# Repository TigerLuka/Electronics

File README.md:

When making a new PCB board, please import corresponding PCB board constraints
from "Board Templates/JLC" if the board is to be manufactured by JLC.

Download git

Create a token in github so you can pull the repository in git bash

------------------------

INSIDE GIT BASH TERMINAL

git clone https://github.com/LSUTigerRacing/Electronics.git

cd Electronics

Highlight and right click on FSAE_ELECTRONICS in git bash terminal to open file location and find KiCAD project

------------------------

MAKE ALL EDITS TO LOCAL COPY HERE

------------------------

OPEN GIT BASH TERMINAL WHEN FINISHED

cd Electronics

git checkout -b "Branch Name"

git add .

git commit -m "Description of work done in commit"

git push -u origin "Branch Name"

DELETE LOCAL COPY

------------------------

REPEAT

------------------------

TO MERGE:

go to branches tab

go to branches that you push

make a pull request

go into pull request

marge if no issues

delete branch 

# FAULT LATCH

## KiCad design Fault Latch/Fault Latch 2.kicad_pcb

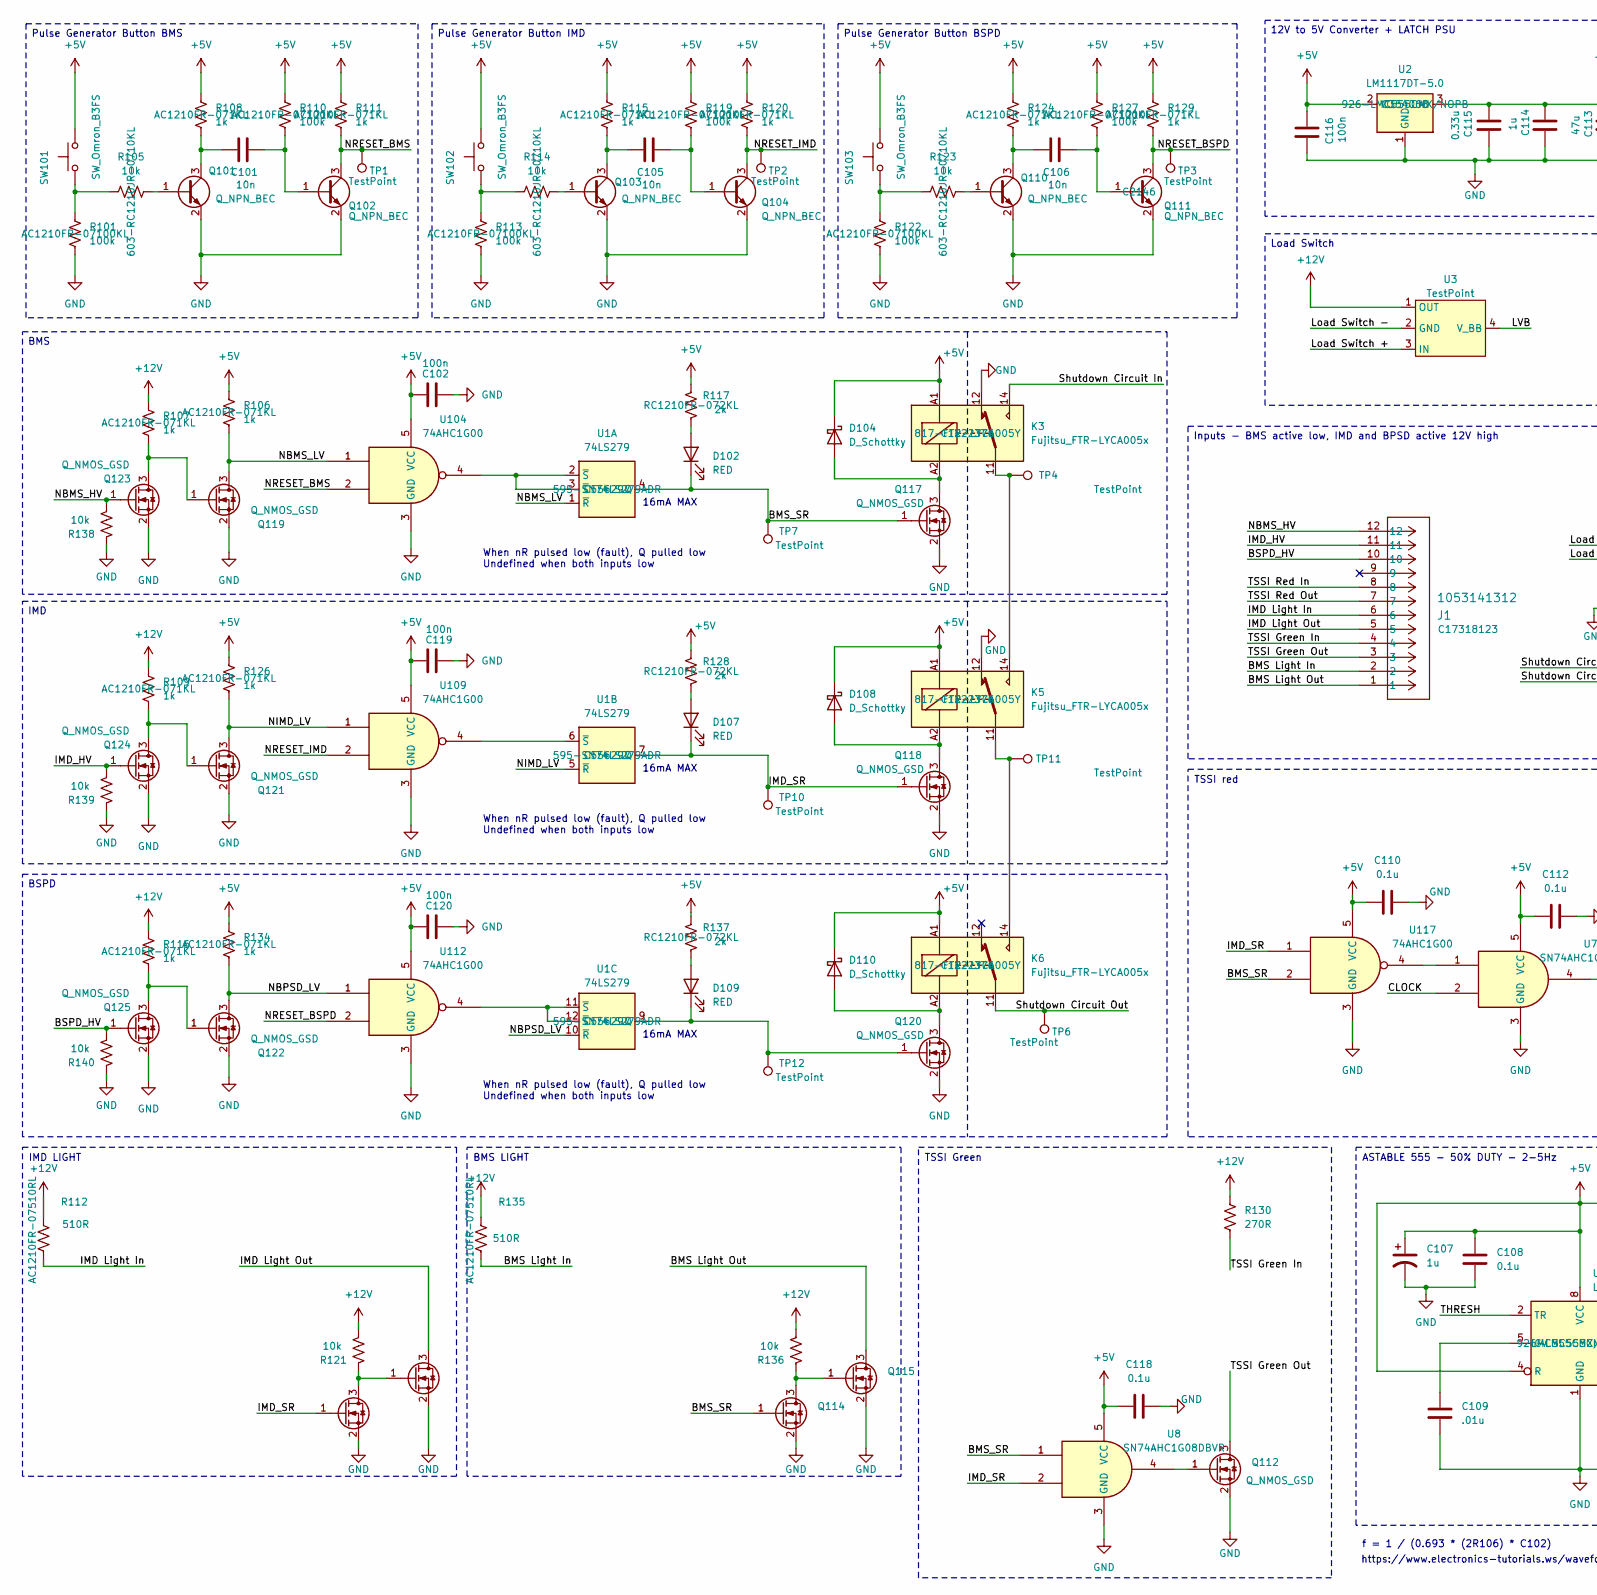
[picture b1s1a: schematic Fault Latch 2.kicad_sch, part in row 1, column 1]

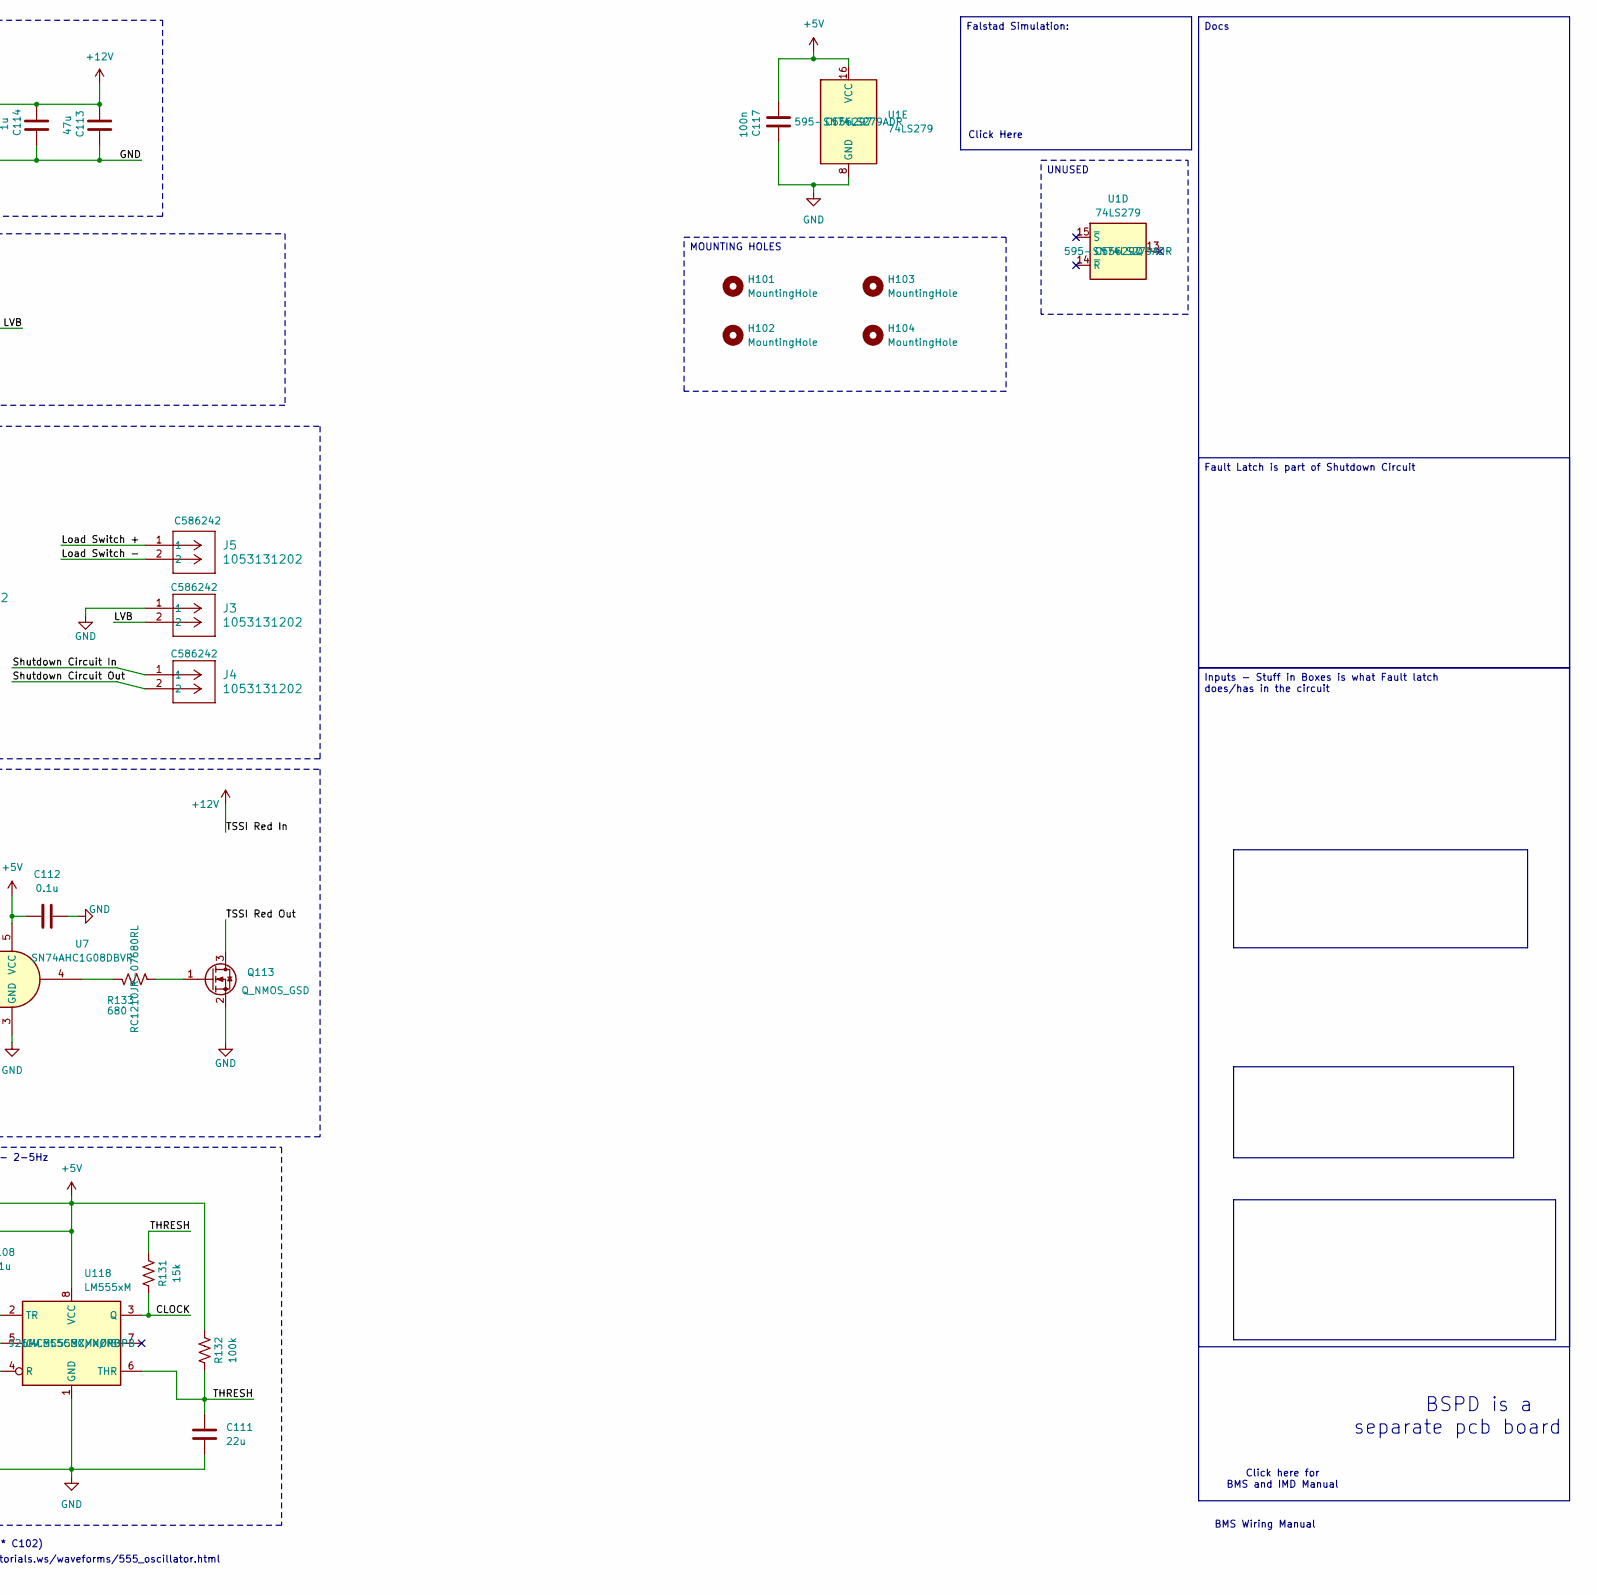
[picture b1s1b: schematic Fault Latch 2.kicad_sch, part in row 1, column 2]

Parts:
C101, C105, C106: 10n; C_0603_1608Metric_Pad1.08x0.95mm_HandSolder; JLC# C1589
C102, C116, C117, C119, C120: 100n; C_0603_1608Metric_Pad1.08x0.95mm_HandSolder; JLC# C1591
C107: 1u; C_0402_1005Metric; JLC# C59782
C108, C110, C112, C118: 0.1u; C_0402_1005Metric; JLC# C133086
C109: .01u; C_0402_1005Metric; JLC# C15195
C111: 22u; C_0402_1005Metric; JLC# C105226
C113: 47u; CP_Elec_6.3x5.4; JLC# C2836440
C114: 1u; C_0805_2012Metric_Pad1.18x1.45mm_HandSolder; JLC# C91186
C115: 0.33u; C_0603_1608Metric_Pad1.08x0.95mm_HandSolder; JLC# C282682
D102, D107, D109: RED; LED_0805_2012Metric_Pad1.15x1.40mm_HandSolder; JLC# C19171391
D104, D108, D110: D_Schottky; D_SMA; JLC# C8678
H101, H102, H103, H104: MountingHole; MountingHole_3.2mm_M3
J1: 1053141312; CONN_SD-105314-100_12_MOL; MOUSER 538-105314-1312
J3, J4, J5: 1053131202; Molex_Nano-Fit_105313-xx02_1x02_P2.50mm_Horizontal; MOUSER 538-105313-1202
K3, K5, K6: Fujitsu_FTR-LYCA005x; Relay_SPDT_Fujitsu_FTR-LYCA005x_FormC_Vertical; MOUSER 817-FTR-LYCA005Y
Q101, Q102, Q103, Q104, Q110, Q111: Q_NPN_BEC; SOT-23; JLC# C2146
Q105, Q106, Q112, Q113, Q114, Q115, Q117, Q118, Q119, Q120, Q121, Q122, Q123, Q124, Q125: Q_NMOS_GSD; SOT-23; JLC# C151421
R101, R110, R113, R119, R122, R127, R132: 100k; R_1210_3225Metric; JLC# C230004
R105, R114, R121, R123, R136, R138, R139, R140: 10k; R_1210_3225Metric; JLC# C137088
R106, R107, R108, R109, R111, R115, R116, R120, R124, R126, R129, R134: 1k; R_1210_3225Metric; JLC# C230096
R112, R135: 510R; R_1210_3225Metric; JLC# C230277
R117, R128, R137: 2k; R_1210_3225Metric; JLC# C137097
R130: 270R; R_1210_3225Metric; JLC# C230144
R131: 15k; R_1210_3225Metric; JLC# C230040
R133: 680; R_1210_3225Metric; JLC# C137071
SW101, SW102, SW103: SW_Omron_B3FS; SW_SPST_Omron_B3FS-100xP; JLC# C271750
TP1, TP2, TP3, TP4, TP6, TP7, TP10, TP11, TP12: TestPoint; TestPoint_Pad_D1.5mm
U1: 74LS279; SOIC-16_3.9x9.9mm_P1.27mm; MOUSER 595-SN74LS279ADR
U2: LM1117DT-5.0; TO-252-3_TabPin2; JLC# C354068
U3: TestPoint; TestPoint_Pad_D1.5mm
U7, U8: SN74AHC1G08DBVR; SOT-23-5; JLC# C7467
U104, U109, U112, U117: 74AHC1G00; SOT-23-5; JLC# C350556
U118: LM555xM; SOIC-8_3.9x4.9mm_P1.27mm; Mouser Part Number 926-LMC555CMX/NOPB; JLC# C90760

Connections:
+5V: C102.1, C107.1, C108.1, C110.2, C112.2, C116.2, C117.1, C118.2, C119.1, C120.1, D104.1 (K), D108.1 (K), D110.1 (K), K3.A1, K5.A1, K6.A1, R106.1, R108.1, R110.1, R111.1, R115.1, R117.2, R119.1, R120.1, R124.1, R126.1, R127.1, R128.2, R129.1, R132.2, R134.1, R137.2, SW101.2, SW102.2, SW103.2, U1.16 (VCC), U2.2 (VO), U7.5 (VCC), U8.5 (VCC), U104.5 (VCC), U109.5 (VCC), U112.5 (VCC), U117.5 (VCC), U118.4 (R), U118.8 (VCC)
+12V: C113.1, C114.1, C115.1, J1.8, R107.1, R109.1, R112.1, R116.1, R121.1, R130.2, R135.1, R136.1, U2.3 (VI), U3.1 (OUT)
/BMS Light In: J1.2, R135.2
/BMS Light Out: J1.1, Q115.3 (D)
/BMS_SR: D102.1 (K), Q114.1 (G), Q117.1 (G), TP7.1, U1.4 (Q), U8.1, U117.2
/BSPD_HV: J1.10, Q125.1 (G), R140.1
/CLOCK: R131.1, U7.2, U118.3 (Q)
/IMD Light In: J1.6, R112.2
/IMD Light Out: J1.5, Q106.3 (D)
/IMD_HV: J1.11, Q124.1 (G), R139.1
/IMD_SR: D107.1 (K), Q105.1 (G), Q118.1 (G), TP10.1, U1.7 (Q), U8.2, U117.1
/LVB: J3.2, U3.4 (V_BB)
/Load Switch +: J5.1, U3.3 (IN)
/Load Switch -: J5.2, U3.2 (GND)
/NBMS_HV: J1.12, Q123.1 (G), R138.1
/NBMS_LV: Q119.3 (D), R106.2, U1.1 (~R), U104.1
/NBPSD_LV: Q122.3 (D), R134.2, U1.10 (~R), U112.1
/NIMD_LV: Q121.3 (D), R126.2, U1.5 (~R), U109.1
/NRESET_BMS: Q102.3 (C), R111.2, TP1.1, U104.2
/NRESET_BSPD: Q111.3 (C), R129.2, TP3.1, U112.2
/NRESET_IMD: Q104.3 (C), R120.2, TP2.1, U109.2
/Shutdown Circuit In: J4.1, K3.14
/Shutdown Circuit Out: J4.2, K6.11, TP6.1
/THRESH: C111.2, R131.2, R132.1, U118.2 (TR), U118.6 (THR)
/TSSI Green In: J1.4, R130.1
/TSSI Green Out: J1.3, Q112.3 (D)
/TSSI Red Out: J1.7, Q113.3 (D)
GND: C102.2, C107.2, C108.2, C109.2, C110.1, C111.1, C112.1, C113.2, C114.2, C115.2, C116.1, C117.2, C118.1, C119.2, C120.2, J3.1, K3.12, K5.12, Q101.2 (E), Q102.2 (E), Q103.2 (E), Q104.2 (E), Q105.2 (S), Q106.2 (S), Q110.2 (E), Q111.2 (E), Q112.2 (S), Q113.2 (S), Q114.2 (S), Q115.2 (S), Q117.2 (S), Q118.2 (S), Q119.2 (S), Q120.2 (S), Q121.2 (S), Q122.2 (S), Q123.2 (S), Q124.2 (S), Q125.2 (S), R101.2, R113.2, R122.2, R138.2, R139.2, R140.2, U1.8 (GND), U2.1 (GND), U7.3 (GND), U8.3 (GND), U104.3 (GND), U109.3 (GND), U112.3 (GND), U117.3 (GND), U118.1 (GND)
unnamed: D102.2 (A), R117.1
unnamed: D104.2 (A), K3.A2, Q117.3 (D)
unnamed: D107.2 (A), R128.1
unnamed: D108.2 (A), K5.A2, Q118.3 (D)
unnamed: D109.2 (A), R137.1
unnamed: D109.1 (K), Q120.1 (G), TP12.1, U1.9 (Q)
unnamed: D110.2 (A), K6.A2, Q120.3 (D)
unnamed: K3.11, K5.14, TP4.1
unnamed: K5.11, K6.14, TP11.1
unnamed: Q101.1 (B), R105.1
unnamed: C101.1, Q101.3 (C), R108.2
unnamed: C101.2, Q102.1 (B), R110.2
unnamed: Q103.1 (B), R114.1
unnamed: C105.1, Q103.3 (C), R115.2
unnamed: C105.2, Q104.1 (B), R119.2
unnamed: Q105.3 (D), Q106.1 (G), R121.2
unnamed: Q110.1 (B), R123.1
unnamed: C106.1, Q110.3 (C), R124.2
unnamed: C106.2, Q111.1 (B), R127.2
unnamed: Q112.1 (G), U8.4
unnamed: Q113.1 (G), R133.1
unnamed: Q114.3 (D), Q115.1 (G), R136.2
unnamed: Q119.1 (G), Q123.3 (D), R107.2
unnamed: Q121.1 (G), Q124.3 (D), R109.2
unnamed: Q122.1 (G), Q125.3 (D), R116.2
unnamed: R101.1, R105.2, SW101.1
unnamed: R113.1, R114.2, SW102.1
unnamed: R122.1, R123.2, SW103.1
unnamed: R133.2, U7.4
unnamed: U1.6 (~S), U109.4
unnamed: U1.2 (~S), U1.3 (~S), U104.4
unnamed: U1.11 (~S), U1.12 (~S), U112.4
unnamed: U7.1, U117.4
unnamed: C109.1, U118.5 (CV)

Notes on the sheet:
16mA MAX
BMS Wiring Manual
When nR pulsed low (fault), Q pulled low Undefined when both inputs low
Click here for BMS and IMD Manual
BSPD is a separate pcb board
f = 1 / (0.693 * (2R106) * C102)
https://www.electronics-tutorials.ws/waveforms/555_oscillator.html
Click Here
UNUSED
Pulse Generator Button BMS
Inputs - Stuff in Boxes is what Fault latch does/has in the circuit
TSSI red
BSPD
BMS
Load Switch
Pulse Generator Button BSPD
TSSI Green
ASTABLE 555 - 50% DUTY - 2-5Hz
Fault Latch is part of Shutdown Circuit
Docs
Pulse Generator Button IMD
12V to 5V Converter + LATCH PSU
MOUNTING HOLES
Inputs - BMS active low, IMD and BPSD active 12V high
BMS LIGHT
IMD
Falstad Simulation:
IMD LIGHT

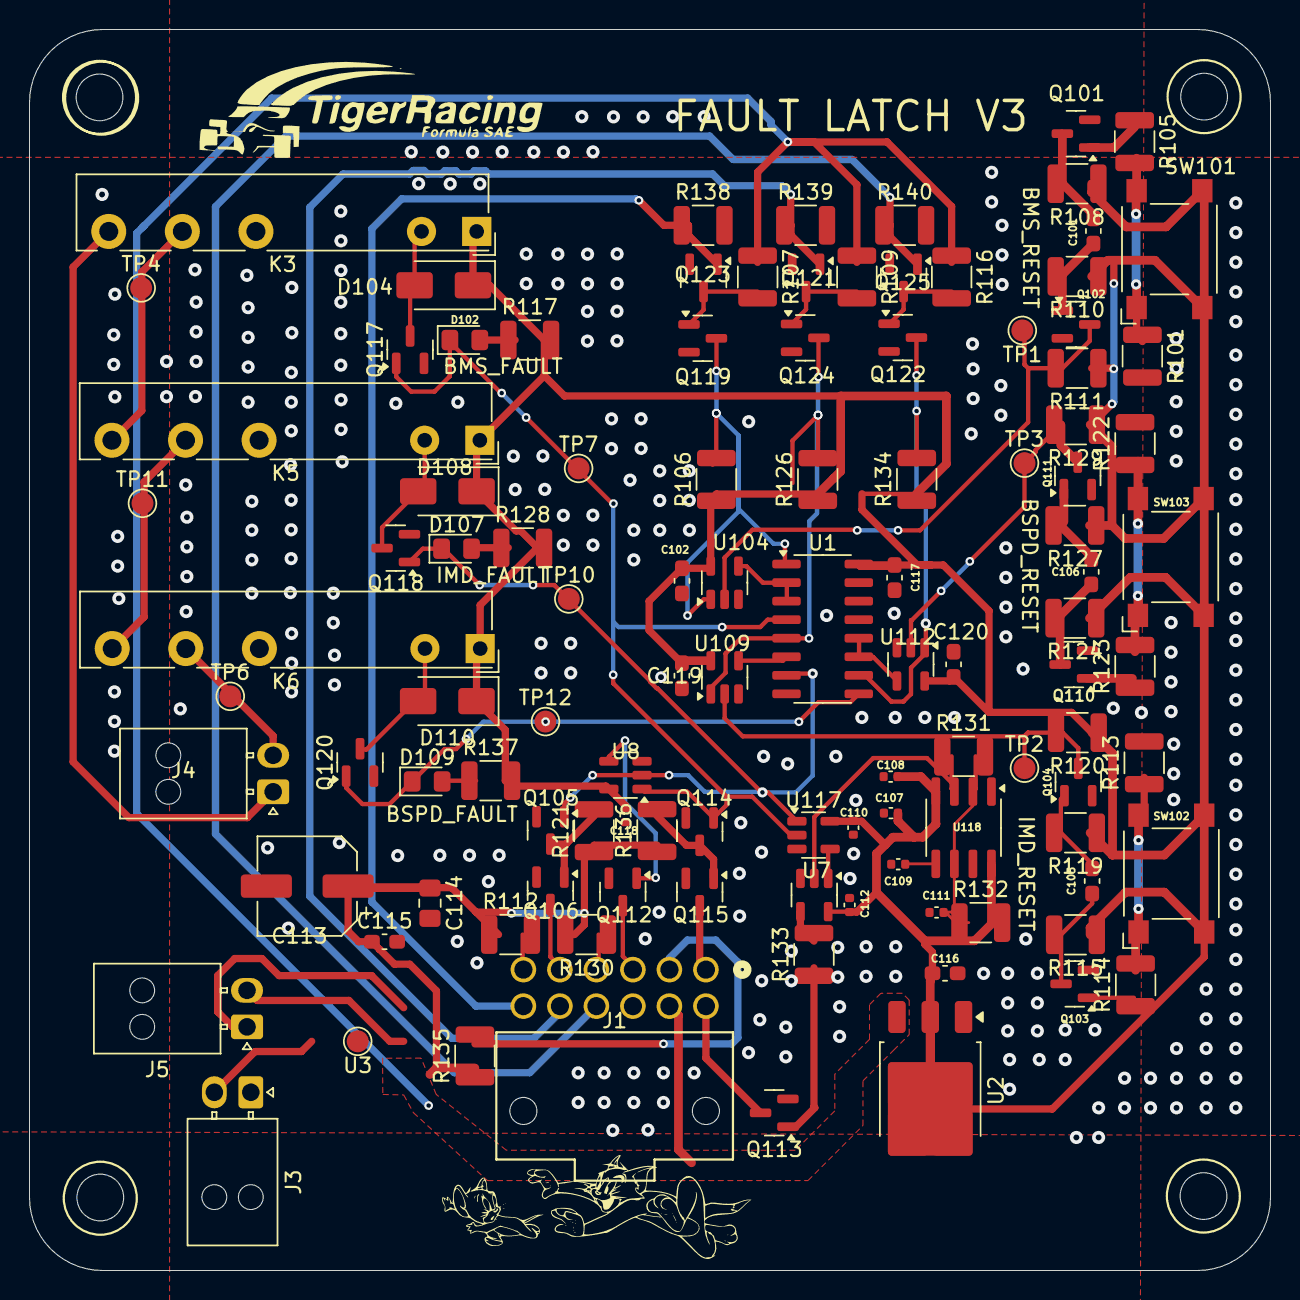
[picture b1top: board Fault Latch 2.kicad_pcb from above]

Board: 2 copper layers, 85.0 x 85.0 mm, 113 parts (0 on the bottom side), 59 nets.

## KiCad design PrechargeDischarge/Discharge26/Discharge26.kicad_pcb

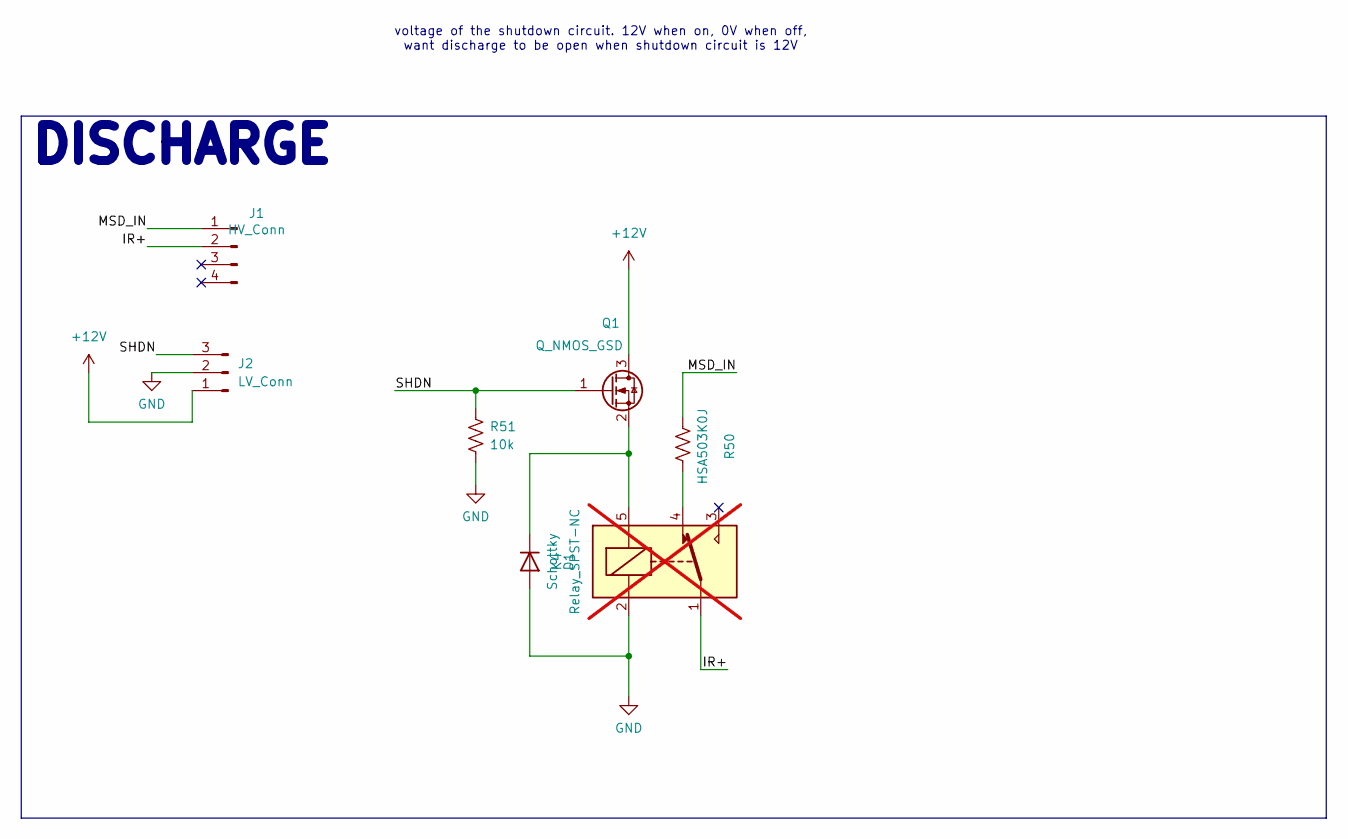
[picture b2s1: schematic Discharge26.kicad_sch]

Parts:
D1: Schottky; D_SMA; JLC C8678
J1: HV_Conn; MicroFit_4pin
J2: LV_Conn; Molex_Nano-Fit_105313-xx03_1x03_P2.50mm_Horizontal; JLC C561764
K4: Relay_SPST-NC; Discharge_relay; not fitted
Q1: Q_NMOS_GSD; SOT-23; JLC# C8545
R50: HSA503K0J; Discharge_Resistor
R51: 10k; R_1206_3216Metric

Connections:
+12V: J2.1, Q1.3 (D)
/IR+: J1.2, K4.1
/MSD_IN: J1.1, R50.2
/SHDN: J2.3, Q1.1 (G), R51.1
GND: D1.2 (A), J2.2, K4.2, R51.2
unnamed: D1.1 (K), K4.5, Q1.2 (S)
unnamed: K4.4, R50.1

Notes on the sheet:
voltage of the shutdown circuit. 12V when on, 0V when off, want discharge to be open when shutdown circuit is 12V
DISCHARGE

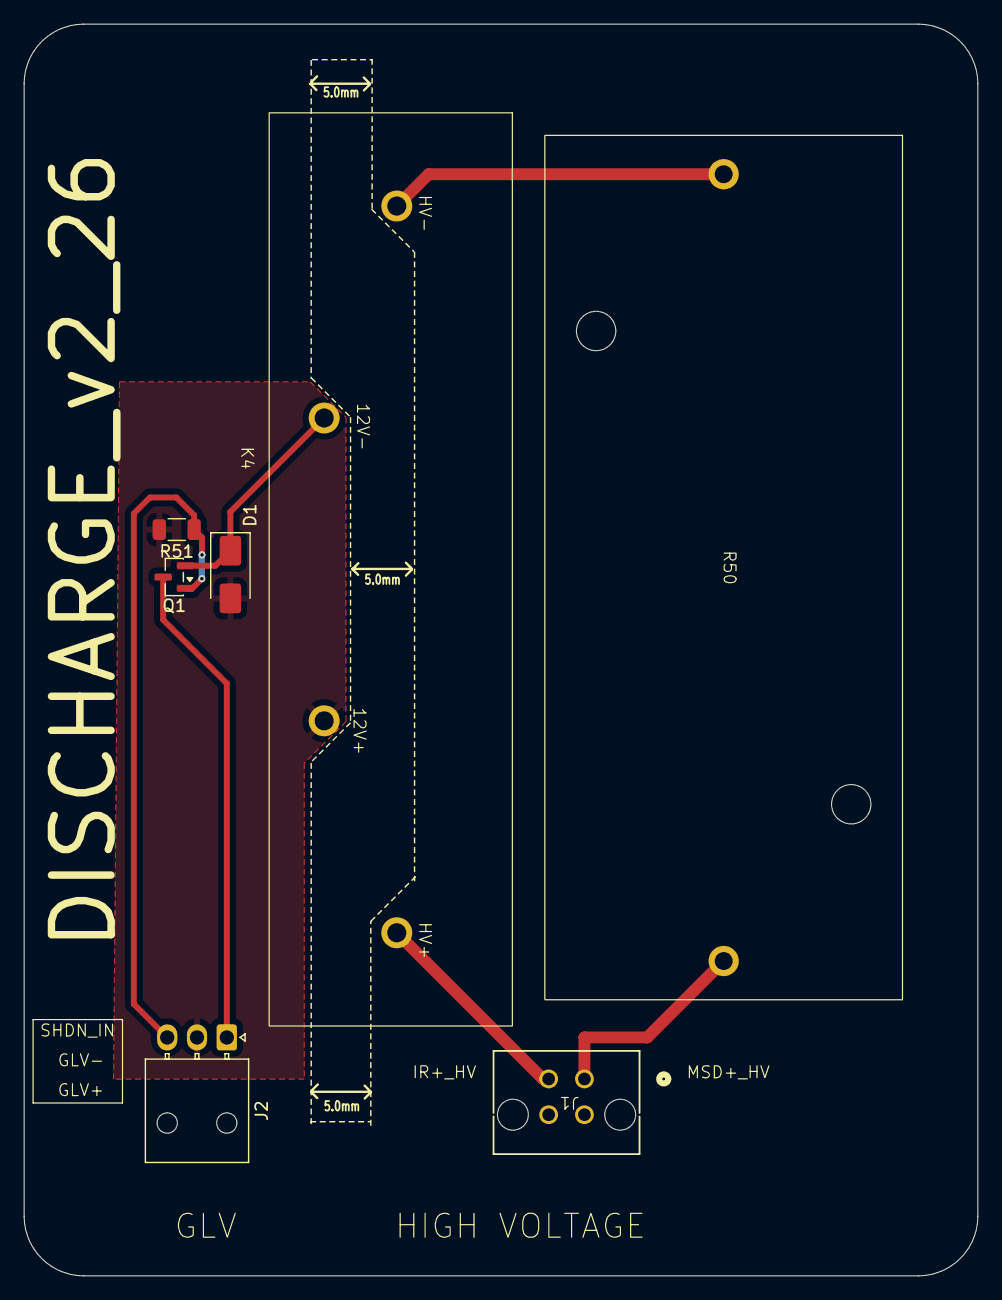
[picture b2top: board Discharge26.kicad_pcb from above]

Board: 2 copper layers, 80.0 x 105.0 mm, 7 parts (0 on the bottom side), 7 nets.

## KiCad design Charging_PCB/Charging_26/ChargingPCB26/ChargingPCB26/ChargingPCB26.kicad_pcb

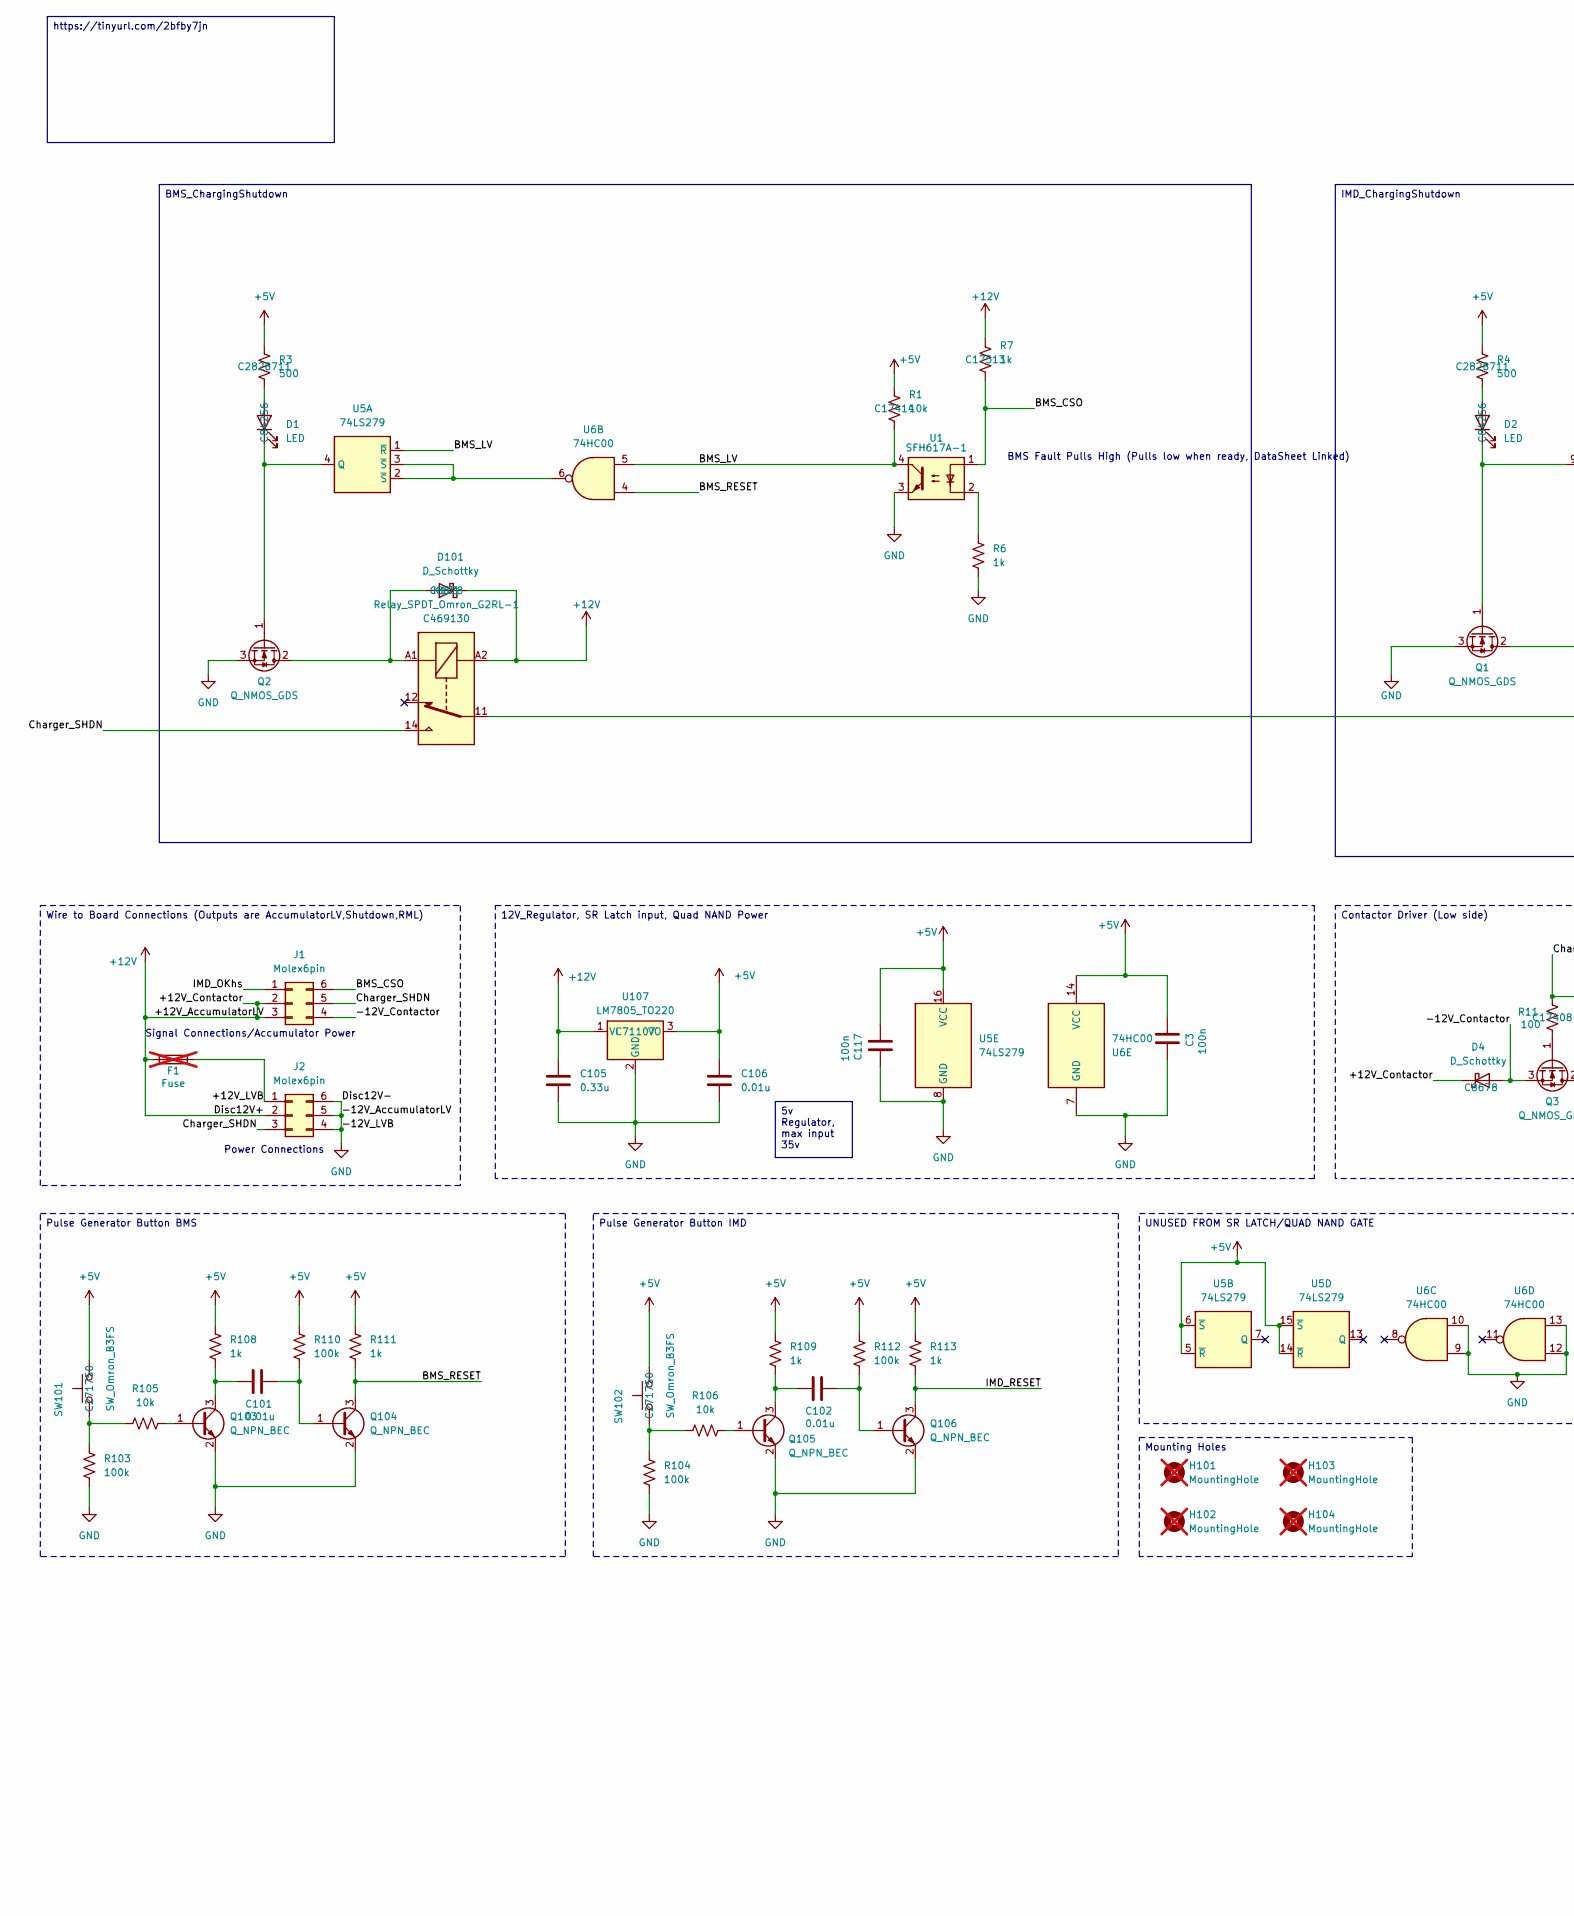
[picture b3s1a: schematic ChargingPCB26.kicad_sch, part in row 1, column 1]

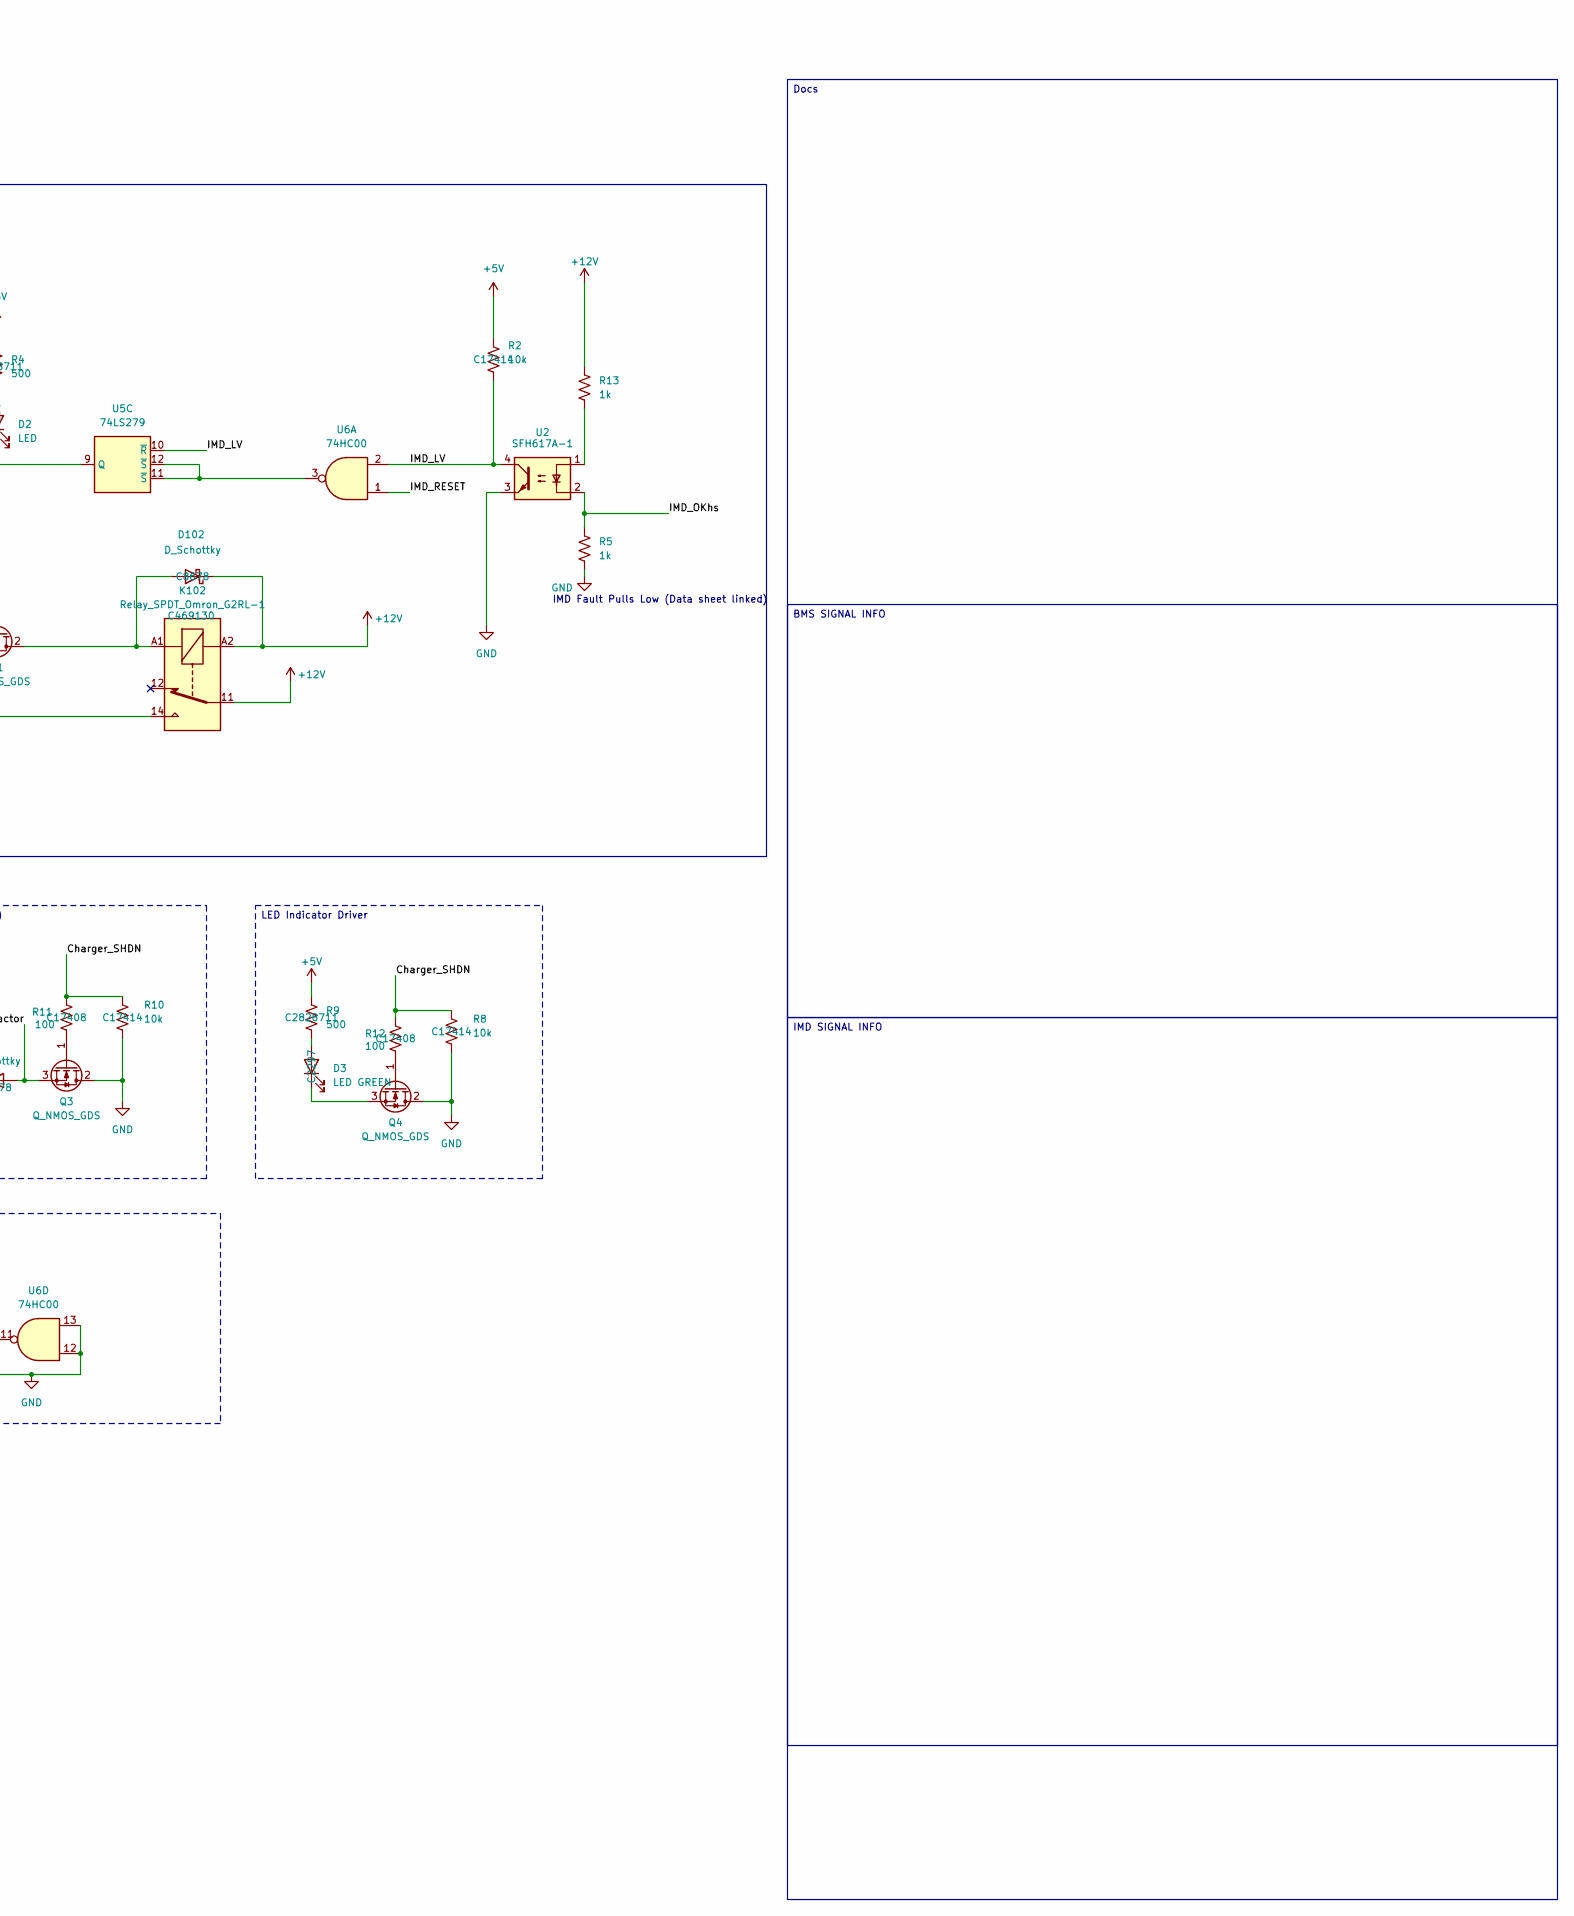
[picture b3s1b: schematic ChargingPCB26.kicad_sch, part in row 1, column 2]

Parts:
C3, C117: 100n; C_0603_1608Metric_Pad1.08x0.95mm_HandSolder; MPN CL10B104KB8NNNC; JLC# C1591
C101, C102, C106: 0.01u; C_0402_1005Metric; MPN CL05B103KB5NNNC; JLC# C15195
C105: 0.33u; C_0402_1005Metric; MPN CC0402KRX5R6BB334; JLC# C107013
D1, D2: LED; LED_0805_2012Metric_Pad1.15x1.40mm_HandSolder; MPN NCD0805R1; JLC# C84256
D3: LED GREEN; LED_0805_2012Metric_Pad1.15x1.40mm_HandSolder; MPN KT-0805G; JLC# C2297
D4, D101, D102: D_Schottky; D_SMA; MPN SS34; JLC# C8678
F1: Fuse; Fuseholder_Blade_Mini_Keystone_3568; Digikey 36-3568-ND; not fitted
H101, H102, H103, H104: MountingHole; MountingHole_2.2mm_M2; not fitted
J1, J2: Molex6pin; Molex_Nano-Fit_105314-xx06_2x03_P2.50mm_Horizontal; MPN 1053141106; Digikey WM3802-ND
K101, K102: Relay_SPDT_Omron_G2RL-1; MPN G2RL-1-DC12; JLC# C469130
Q1, Q2, Q3, Q4: Q_NMOS_GDS; TO-251-3_Vertical; JLC# C3278986
Q103, Q104, Q105, Q106: Q_NPN_BEC; SOT-23; MPN S8050 J3Y(RANGE:200-350); JLC# C2146
R1, R2, R8, R10, R105, R106: 10k; R_0805_2012Metric_Pad1.20x1.40mm_HandSolder; MPN 0805W8F1002T5E; JLC# C17414
R3, R4, R9: 500; R_0805_2012Metric_Pad1.20x1.40mm_HandSolder; MPN ARG05BTC5000; JLC# C2828711
R5, R6, R13: 1k; R_0805_2012Metric_Pad1.20x1.40mm_HandSolder; MPN 0805W8F1001T5E; Digikey 1.00KXBK-ND
R7, R108, R109, R111, R113: 1k; R_0805_2012Metric_Pad1.20x1.40mm_HandSolder; MPN 0805W8F1001T5E; JLC# C17513
R11, R12: 100; R_0805_2012Metric_Pad1.20x1.40mm_HandSolder; JLC# C17408
R103, R104, R110, R112: 100k; R_0805_2012Metric_Pad1.20x1.40mm_HandSolder; MPN 0805W8F1003T5E; JLC# C149504
SW101, SW102: SW_Omron_B3FS; SW_SPST_Omron_B3FS-100xP; MPN B3FS-1000P; JLC# C271750
U1, U2: SFH617A-1; DIP-4_W7.62mm; MPN PC817X2NSZW; Digikey 58-SFH615A-1X-ND
U5: 74LS279; DIP-16_W7.62mm; MPN SN74LS279AN; Digikey 296-3684-5-ND
U6: 74HC00; DIP-14_W7.62mm; MPN SN74HC00N; JLC# C2902
U107: LM7805_TO220; TO-220-3_Vertical; MPN LM7805L-TF3-T; JLC# C71107

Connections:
+5V: C3.1, C106.1, C117.1, R1.1, R2.1, R3.1, R4.1, R9.1, R108.1, R109.1, R110.1, R111.1, R112.1, R113.1, SW101.2, SW102.2, U5.5 (~R), U5.6 (~S), U5.14 (~R), U5.15 (~S), U5.16 (VCC), U6.14 (VCC), U107.3 (VO)
+12V: C105.1, D4.1 (K), D101.1 (K), D102.1 (K), F1.1, J1.2, J1.3, J2.2, K101.A2, K102.11, K102.A2, R7.1, R13.1, U107.1 (VI)
/+12V_LVB: F1.2, J2.1
/-12V_Contactor: D4.2 (A), J1.4, Q3.3 (S)
/BMS_CSO: J1.6, R7.2, U1.1
/BMS_LV: R1.2, U1.4, U5.1 (~R), U6.5
/BMS_RESET: Q104.3 (C), R111.2, U6.4
/Charger_SHDN: J1.5, J2.3, K101.14, R8.1, R10.1, R11.1, R12.1
/IMD_LV: R2.2, U2.4, U5.10 (~R), U6.2
/IMD_OKhs: J1.1, R5.1, U2.2
/IMD_RESET: Q106.3 (C), R113.2, U6.1
GND: C3.2, C105.2, C106.2, C117.2, J2.4, J2.5, J2.6, Q1.3 (S), Q2.3 (S), Q3.2 (D), Q4.2 (D), Q103.2 (E), Q104.2 (E), Q105.2 (E), Q106.2 (E), R5.2, R6.2, R8.2, R10.2, R103.2, R104.2, U1.3, U2.3, U5.8 (GND), U6.7 (GND), U6.9, U6.10, U6.12, U6.13, U107.2 (GND)
unnamed: D1.2 (A), R3.2
unnamed: D1.1 (K), Q2.1 (G), U5.4 (Q)
unnamed: D2.2 (A), R4.2
unnamed: D2.1 (K), Q1.1 (G), U5.9 (Q)
unnamed: D3.2 (A), R9.2
unnamed: D3.1 (K), Q4.3 (S)
unnamed: D101.2 (A), K101.A1, Q2.2 (D)
unnamed: D102.2 (A), K102.A1, Q1.2 (D)
unnamed: K101.11, K102.14
unnamed: Q3.1 (G), R11.2
unnamed: Q4.1 (G), R12.2
unnamed: Q103.1 (B), R105.1
unnamed: C101.1, Q103.3 (C), R108.2
unnamed: C101.2, Q104.1 (B), R110.2
unnamed: Q105.1 (B), R106.1
unnamed: C102.1, Q105.3 (C), R109.2
unnamed: C102.2, Q106.1 (B), R112.2
unnamed: R6.1, U1.2
unnamed: R13.2, U2.1
unnamed: R103.1, R105.2, SW101.1
unnamed: R104.1, R106.2, SW102.1
unnamed: U5.2 (~S), U5.3 (~S), U6.6
unnamed: U5.11 (~S), U5.12 (~S), U6.3

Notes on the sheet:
Power Connections
Signal Connections/Accumulator Power
BMS Fault Pulls High (Pulls low when ready, DataSheet Linked)
IMD Fault Pulls Low (Data sheet linked)
Contactor Driver (Low side)
IMD SIGNAL INFO
UNUSED FROM SR LATCH/QUAD NAND GATE
5v Regulator, max input 35v
Mounting Holes
BMS SIGNAL INFO
BMS_ChargingShutdown
Pulse Generator Button BMS
Docs
IMD_ChargingShutdown
LED Indicator Driver
12V_Regulator, SR Latch input, Quad NAND Power
Wire to Board Connections (Outputs are AccumulatorLV,Shutdown,RML)
Pulse Generator Button IMD
https://tinyurl.com/2bfby7jn
